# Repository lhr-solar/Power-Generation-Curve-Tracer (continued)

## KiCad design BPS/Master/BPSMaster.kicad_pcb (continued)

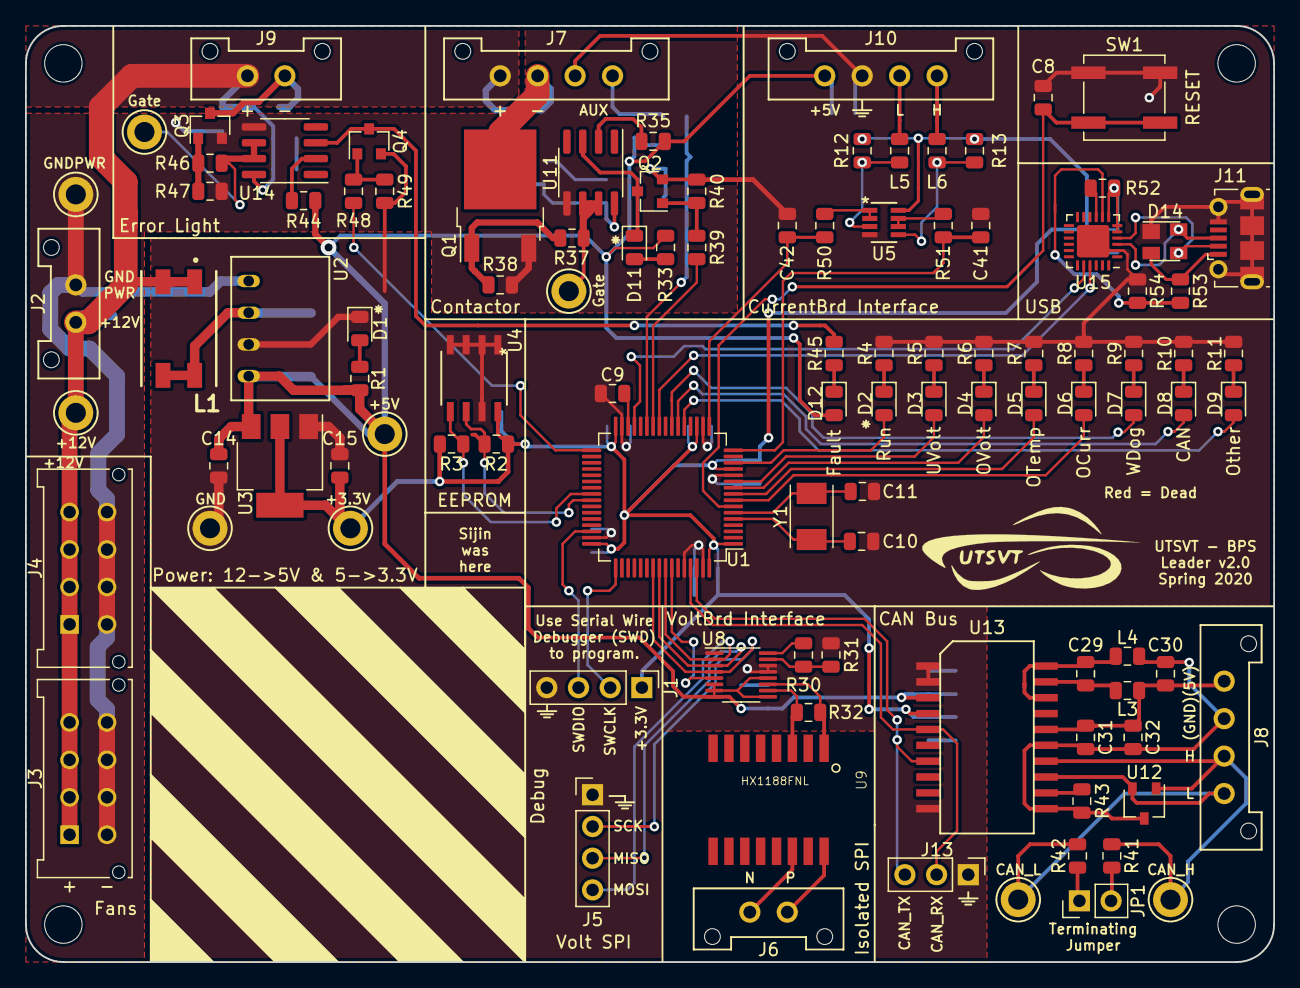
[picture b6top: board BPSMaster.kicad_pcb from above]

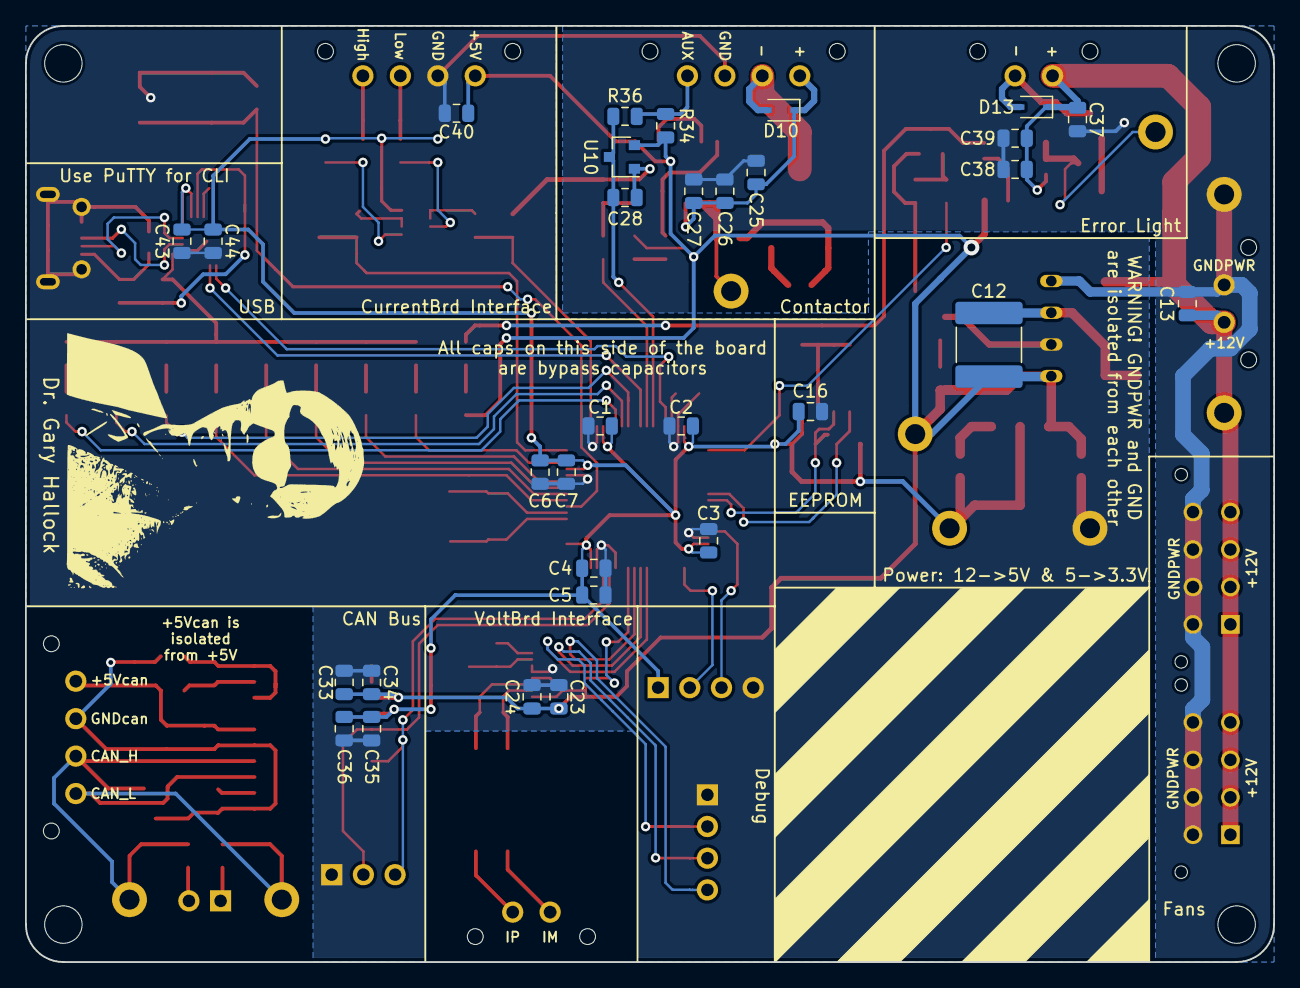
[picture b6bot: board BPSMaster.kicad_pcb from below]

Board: 2 copper layers, 100.0 x 75.0 mm, 140 parts (31 on the bottom side), 85 nets.

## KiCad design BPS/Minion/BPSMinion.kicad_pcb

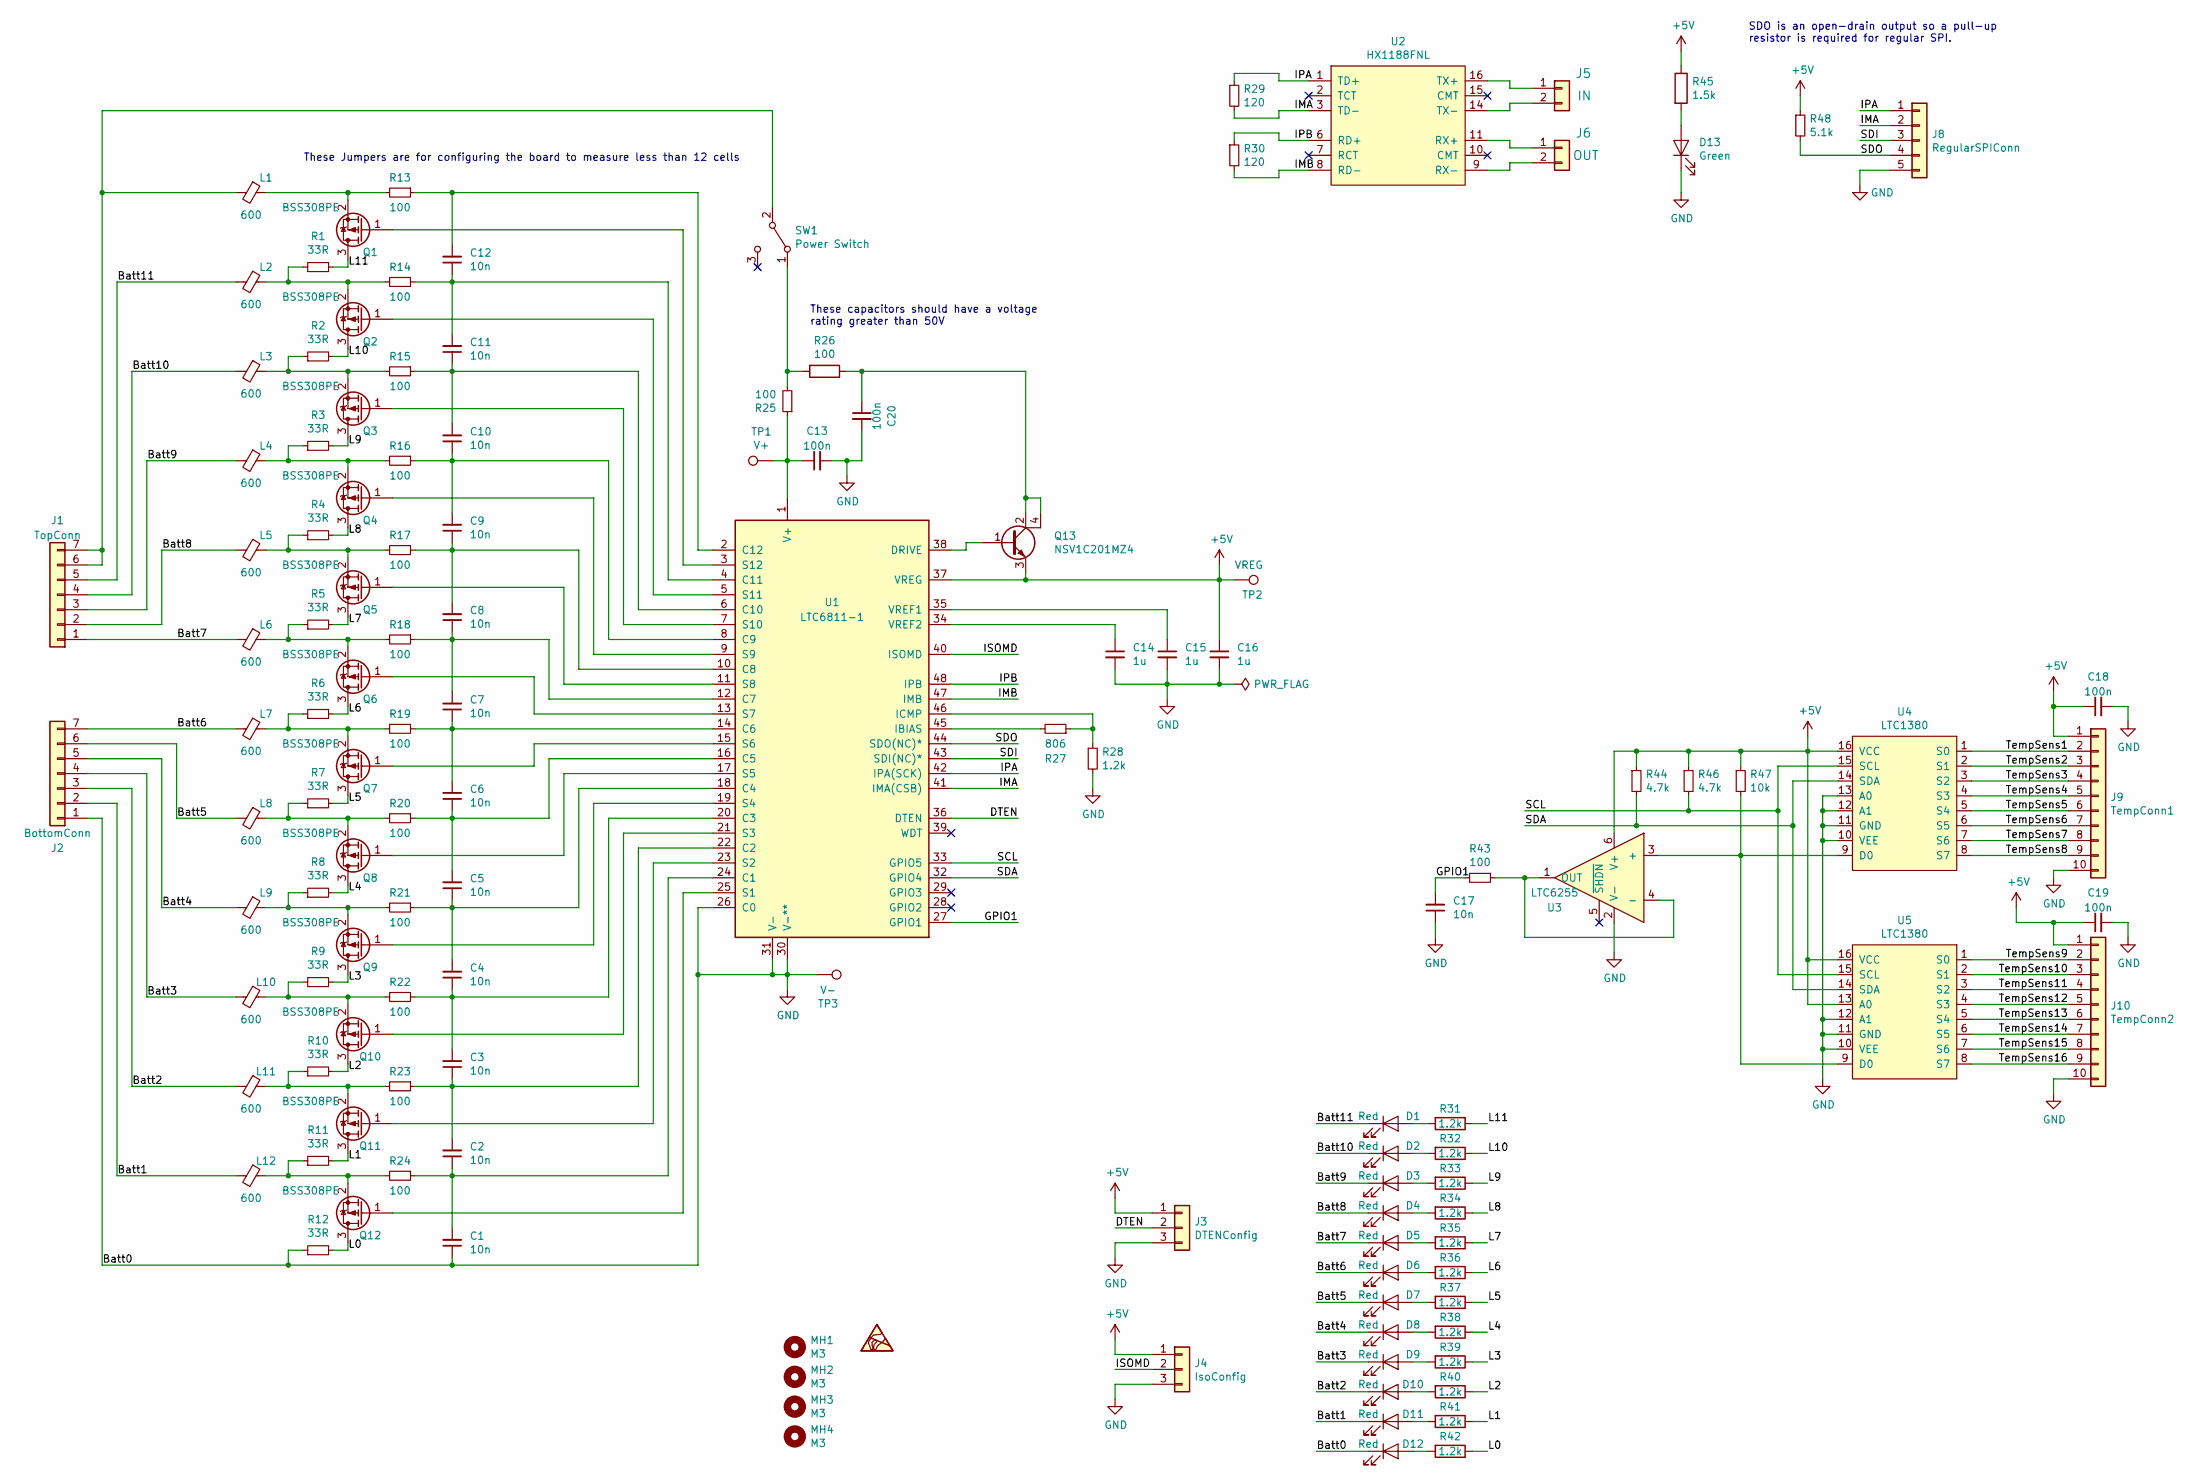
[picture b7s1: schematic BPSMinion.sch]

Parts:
C1, C2, C3, C4, C5, C6, C7, C8, C9, C10, C11, C12, C17: 10n; C_0805_2012Metric
C13, C20: 100n; C_0805_2012Metric; Tolerance 10%; Voltage 100VDC
C14, C15: 1u; C_0805_2012Metric; Tolerance 10%; Voltage 50VDC
C16: 1u; C_0805_2012Metric
C18, C19: 100n; C_0805_2012Metric; Tolerance 10%; Voltage 50VDC
D1, D2, D3, D4, D5, D6, D7, D8, D9, D10, D11, D12: Red; LED_0805_2012Metric
D13: Green; LED_0805_2012Metric
J1: TopConn; Molex_Micro-Fit_3.0_43650-0700_1x07_P3.00mm_Horizontal
J2: BottomConn; Molex_Micro-Fit_3.0_43650-0700_1x07_P3.00mm_Horizontal
J3: DTENConfig; PinHeader_1x03_P2.54mm_Vertical
J4: IsoConfig; PinHeader_1x03_P2.54mm_Vertical
J5: IN; Molex_Micro-Fit_3.0_43650-0200_1x02_P3.00mm_Horizontal
J6: OUT; Molex_Micro-Fit_3.0_43650-0200_1x02_P3.00mm_Horizontal
J8: RegularSPIConn; PinHeader_1x05_P2.54mm_Vertical
J9: TempConn1; PinHeader_1x10_P2.54mm_Vertical
J10: TempConn2; PinHeader_1x10_P2.54mm_Vertical
L1, L2, L3, L4, L5, L6, L7, L8, L9, L10, L11, L12: 600; L_0805_2012Metric
MH1, MH2, MH3, MH4: M3; MountingHole_3mm
Q1, Q2, Q3, Q4, Q5, Q6, Q7, Q8, Q9, Q10, Q11, Q12: BSS308PE; SOT-23
Q13: NSV1C201MZ4; SOT-223
R1, R2, R3, R4, R5, R6, R7, R8, R9, R10, R11, R12: 33R; R_2512_6332Metric
R13, R14, R15, R16, R17, R18, R19, R20, R21, R22, R23, R24, R25, R26, R43: 100; R_0805_2012Metric
R27: 806; R_0805_2012Metric
R28, R31, R32, R33, R34, R35, R36, R37, R38, R39, R40, R41, R42: 1.2k; R_0805_2012Metric
R29, R30: 120; R_0805_2012Metric
R44, R46: 4.7k; R_0805_2012Metric
R45: 1.5k; R_0805_2012Metric
R47: 10k; R_0805_2012Metric
R48: 5.1k; R_0805_2012Metric
SW1: Power Switch; SW_CuK_OS102011MA1QN1_SPDT_Angled
TP1: V+; TestPoint_Keystone_5005-5009_Compact
TP2: VREG; TestPoint_Keystone_5005-5009_Compact
TP3: V-; TestPoint_Keystone_5005-5009_Compact
U1: LTC6811-1; LTC6811HG-1-PBF
U2: HX1188FNL; HXXXX
U3: LTC6255; LTC6255CS6-TRMPBF
U4, U5: LTC1380; LTC1380CS-PBF

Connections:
+5V: C16.1, C18.1, C19.1, J3.1, J4.1, J9.1, J10.1, Q13.3 (E), R44.1, R45.1, R46.1, R47.1, R48.1, TP2.1, U1.37 (VREG), U3.6 (V+), U4.16 (VCC), U5.13 (A0), U5.16 (VCC)
/Batt1: D11.1 (K), J2.2, L12.2
/Batt2: D10.1 (K), J2.3, L11.2
/Batt3: D9.1 (K), J2.4, L10.2
/Batt4: D8.1 (K), J2.5, L9.2
/Batt5: D7.1 (K), J2.6, L8.2
/Batt6: D6.1 (K), J2.7, L7.2
/Batt7: D5.1 (K), J1.1, L6.2
/Batt8: D4.1 (K), J1.2, L5.2
/Batt9: D3.1 (K), J1.3, L4.2
/Batt10: D2.1 (K), J1.4, L3.2
/Batt11: D1.1 (K), J1.5, L2.2
/DTEN: J3.2, U1.36 (DTEN)
/GPIO1: C17.2, R43.2, U1.27 (GPIO1)
/IMA: J8.2, R29.2, U1.41 (IMA(CSB)), U2.3 (TD-)
/IMB: R30.2, U1.47 (IMB), U2.8 (RD-)
/IPA: J8.1, R29.1, U1.42 (IPA(SCK)), U2.1 (TD+)
/IPB: R30.1, U1.48 (IPB), U2.6 (RD+)
/ISOMD: J4.2, U1.40 (ISOMD)
/L0: Q12.3 (D), R12.2, R42.1
/L1: Q11.3 (D), R11.2, R41.1
/L2: Q10.3 (D), R10.2, R40.1
/L3: Q9.3 (D), R9.2, R39.1
/L4: Q8.3 (D), R8.2, R38.1
/L5: Q7.3 (D), R7.2, R37.1
/L6: Q6.3 (D), R6.2, R36.1
/L7: Q5.3 (D), R5.2, R35.1
/L8: Q4.3 (D), R4.2, R34.1
/L9: Q3.3 (D), R3.2, R33.1
/L10: Q2.3 (D), R2.2, R32.1
/L11: Q1.3 (D), R1.2, R31.1
/SCL: R46.2, U1.33 (GPIO5), U4.15 (SCL), U5.15 (SCL)
/SDA: R44.2, U1.32 (GPIO4), U4.14 (SDA), U5.14 (SDA)
/SDI: J8.3, U1.43 (SDI(NC)*)
/SDO: J8.4, R48.2, U1.44 (SDO(NC)*)
/TempSens1: J9.2, U4.1 (S0)
/TempSens2: J9.3, U4.2 (S1)
/TempSens3: J9.4, U4.3 (S2)
/TempSens4: J9.5, U4.4 (S3)
/TempSens5: J9.6, U4.5 (S4)
/TempSens6: J9.7, U4.6 (S5)
/TempSens7: J9.8, U4.7 (S6)
/TempSens8: J9.9, U4.8 (S7)
/TempSens9: J10.2, U5.1 (S0)
/TempSens10: J10.3, U5.2 (S1)
/TempSens11: J10.4, U5.3 (S2)
/TempSens12: J10.5, U5.4 (S3)
/TempSens13: J10.6, U5.5 (S4)
/TempSens14: J10.7, U5.6 (S5)
/TempSens15: J10.8, U5.7 (S6)
/TempSens16: J10.9, U5.8 (S7)
GND: C1.1, C13.2, C14.2, C15.2, C16.2, C17.1, C18.2, C19.2, C20.2, D12.1 (K), D13.1 (K), J2.1, J3.3, J4.3, J8.5, J9.10, J10.10, R12.1, R28.2, TP3.1, U1.26 (C0), U1.30 (V-**), U1.31 (V-), U3.2 (V-), U4.10 (VEE), U4.11 (GND), U4.12 (A1), U4.13 (A0), U5.10 (VEE), U5.11 (GND), U5.12 (A1)
unnamed: C1.2, C2.1, R24.1, U1.24 (C1)
unnamed: C2.2, C3.1, R23.1, U1.22 (C2)
unnamed: C3.2, C4.1, R22.1, U1.20 (C3)
unnamed: C4.2, C5.1, R21.1, U1.18 (C4)
unnamed: C5.2, C6.1, R20.1, U1.16 (C5)
unnamed: C6.2, C7.1, R19.1, U1.14 (C6)
unnamed: C7.2, C8.1, R18.1, U1.12 (C7)
unnamed: C8.2, C9.1, R17.1, U1.10 (C8)
unnamed: C9.2, C10.1, R16.1, U1.8 (C9)
unnamed: C10.2, C11.1, R15.1, U1.6 (C10)
unnamed: C11.2, C12.1, R14.1, U1.4 (C11)
unnamed: C12.2, R13.1, U1.2 (C12)
unnamed: C13.1, R25.1, TP1.1, U1.1 (V+)
unnamed: C14.1, U1.34 (VREF2)
unnamed: C15.1, U1.35 (VREF1)
unnamed: C20.1, Q13.2 (C), Q13.4 (C), R26.1
unnamed: D1.2 (A), R31.2
unnamed: D2.2 (A), R32.2
unnamed: D3.2 (A), R33.2
unnamed: D4.2 (A), R34.2
unnamed: D5.2 (A), R35.2
unnamed: D6.2 (A), R36.2
unnamed: D7.2 (A), R37.2
unnamed: D8.2 (A), R38.2
unnamed: D9.2 (A), R39.2
unnamed: D10.2 (A), R40.2
unnamed: D11.2 (A), R41.2
unnamed: D12.2 (A), R42.2
unnamed: D13.2 (A), R45.2
unnamed: J1.6, J1.7, L1.2, SW1.2 (B)
unnamed: J5.1, U2.16 (TX+)
unnamed: J5.2, U2.14 (TX-)
unnamed: J6.1, U2.11 (RX+)
unnamed: J6.2, U2.9 (RX-)
unnamed: L1.1, Q1.2 (S), R13.2
unnamed: L2.1, Q2.2 (S), R1.1, R14.2
unnamed: L3.1, Q3.2 (S), R2.1, R15.2
unnamed: L4.1, Q4.2 (S), R3.1, R16.2
unnamed: L5.1, Q5.2 (S), R4.1, R17.2
unnamed: L6.1, Q6.2 (S), R5.1, R18.2
unnamed: L7.1, Q7.2 (S), R6.1, R19.2
unnamed: L8.1, Q8.2 (S), R7.1, R20.2
unnamed: L9.1, Q9.2 (S), R8.1, R21.2
unnamed: L10.1, Q10.2 (S), R9.1, R22.2
unnamed: L11.1, Q11.2 (S), R10.1, R23.2
unnamed: L12.1, Q12.2 (S), R11.1, R24.2
unnamed: Q1.1 (G), U1.3 (S12)
unnamed: Q2.1 (G), U1.5 (S11)
unnamed: Q3.1 (G), U1.7 (S10)
unnamed: Q4.1 (G), U1.9 (S9)
unnamed: Q5.1 (G), U1.11 (S8)
unnamed: Q6.1 (G), U1.13 (S7)
unnamed: Q7.1 (G), U1.15 (S6)
unnamed: Q8.1 (G), U1.17 (S5)
unnamed: Q9.1 (G), U1.19 (S4)
unnamed: Q10.1 (G), U1.21 (S3)
unnamed: Q11.1 (G), U1.23 (S2)
unnamed: Q12.1 (G), U1.25 (S1)
unnamed: Q13.1 (B), U1.38 (DRIVE)
unnamed: R25.2, R26.2, SW1.1 (A)
unnamed: R27.1, R28.1, U1.46 (ICMP)
unnamed: R27.2, U1.45 (IBIAS)
unnamed: R43.1, U3.1 (OUT), U3.4 (-)
unnamed: R47.2, U3.3 (+), U4.9 (D0), U5.9 (D0)

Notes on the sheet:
SDO is an open-drain output so a pull-up resistor is required for regular SPI.
These Jumpers are for configuring the board to measure less than 12 cells
These capacitors should have a voltage rating greater than 50V

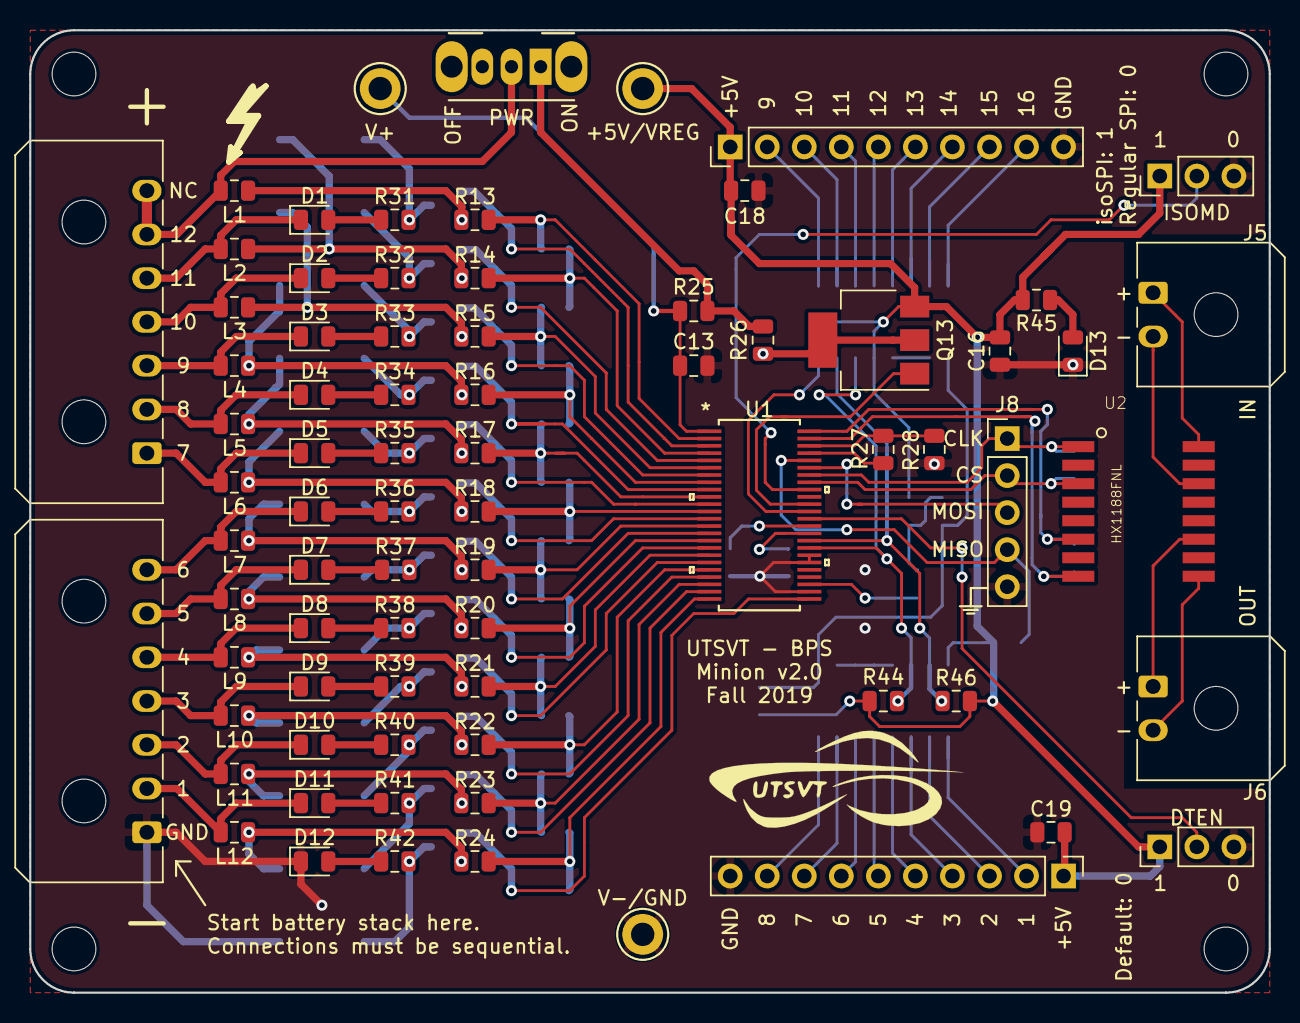
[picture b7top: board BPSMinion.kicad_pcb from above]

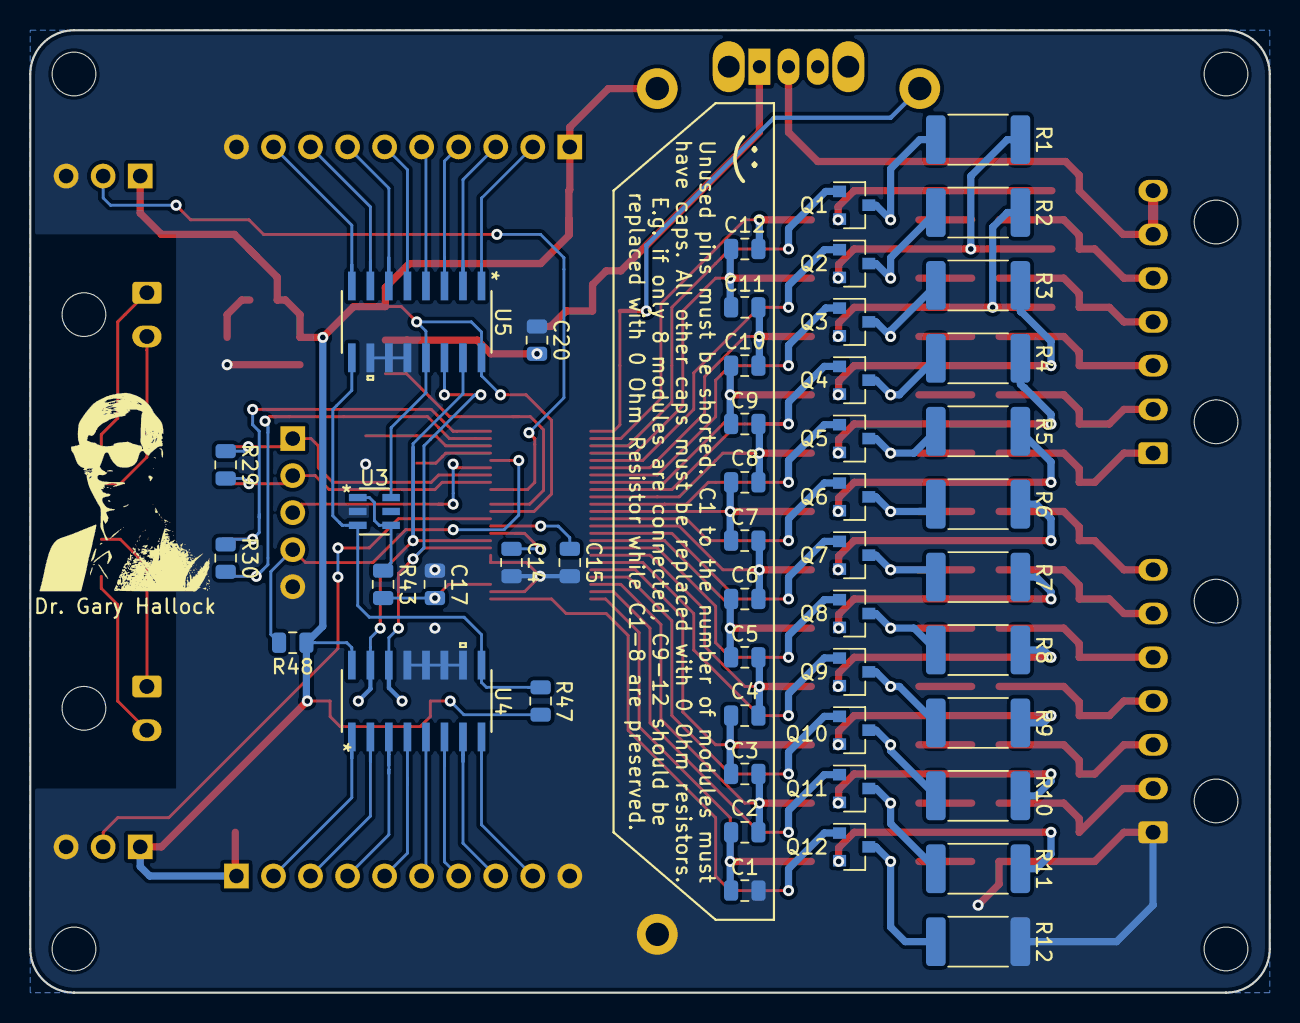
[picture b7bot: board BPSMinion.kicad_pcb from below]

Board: 2 copper layers, 85.0 x 66.0 mm, 128 parts (48 on the bottom side), 116 nets.
